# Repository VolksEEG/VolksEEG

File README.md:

# VolksEEG: Acheiving the Promise of Open Source Medical Devices

In a nutshell...

* *The VolksEEG project is creating an open-source
electroencephalogram (EEG) machine, fully-functional for clinical or research use.*

* *The final device will obtain clearance by the USA FDA, and CE marking
(the equivalent of FDA clearance in the EU).*

* *Currently, no other
open-source electronic medical device (that we know of) has full regulatory clearance*

* *All hardware and software designs will be freely available ([free as in speech and as in beer](https://www.howtogeek.com/howto/31717/what-do-the-phrases-free-speech-vs.-free-beer-really-mean)).*

VolksEEG will be the first in a line of open-source medical
devices that will enable a quantum leap in device safety, cost reduction, and innovation.

To sign up for updates about the project, head to [volkseeg.org](https://volkseeg.org).

Here is a video showing the real-time display of 32 waveform channels, from a UI proof-of-concept application:

<https://user-images.githubusercontent.com/58418/132131736-32bca075-f591-47dc-b3fa-c07dddc95de6.mp4>

(The final device will display EEG channels rather than sine waves, of course.)

## Qs & As

You might have a few questions; we have answers, click on the links below to read the:

* [Why are open-source medical devices a good
idea?](#why-are-open-source-medical-devices-a-good-idea)

* [Medical devices? Do you actually know what you're doing?](#do-you-actually-know-what-you-are-doing)

* [Why an EEG machine?](#why-start-with-an-eeg-machine)

* [What needs to be done?](#what-needs-to-be-done)

* [How can I help?](#how-can-i-help)

* [Project planning](#Project-planning)

* [Wait... don't medical devices need to have full requirements and specifications before starting any development?](#where-are-the-detailed-requirements-and-specs)

---

## Why are open-source medical devices a good idea?

Open-source medical devices will provide increased safety, increased
innovation, and reduced device costs.

### Increased Safety

Like all devices, medical devices have become much more complex over
time. *Unlike* all devices, medical devices are often safety- or
life-critical.

As complexity increases, it becomes ever easier to overlook
small design flaws during development, often leading to recalls
later – each year, hundreds of thousands of devices are subject to Class
I recalls, the FDA’s most serious class of recall, reserved for issues
that could cause serious injury or death.

Design flaws are detected by *design reviews*. A core challenge of medical
device safety is ensuring the adequacy of design reviews – both in the
person-hours spent, and the expertise of the reviewers. While design
reviews of proprietary medical devices typically involve only a handful
of reviewers, open-source devices can leverage the eyeballs of myriad
reviewers with a wide variety of expertise; as stated in *The Cathedral
and the Bazaar,* "given enough eyeballs, all bugs are shallow".

### Increased Innovation

Innovation in medical devices is painstakingly slow – compared to
devices from decades ago, most of today’s devices may have more
convenience features, but by-and-large their core functionality is the
same as it was decades ago.

There are several structural issues that impede device innovation. One
of these is the barrier between device companies and
clinicians/researchers. By building proprietary systems using a
conventional profit-only model, manufacturers make it difficult or
impossible for researchers to try new techniques and technologies that
could lead to breakthroughs.

Open-source designs will accelerate innovative research in hospitals and
universities. Investigators will be able to access data from devices,
and even make changes to devices to test new concepts. (To ensure
safety, the FDA and all hospitals have strict rules around how altered
devices can be used.)

In fact... VolksEEG will contain essentially the same circuitry as will be
used in our clinical EEG, and will directly fill a currently-unmet need for research into making anesthesia safer.

### Reduced Device Costs

Medical devices are expensive. There are various reasons for this – some
of these contribute to better patient care, but many don’t. A simple
illustration of this can be seen in the title of a recent journal
article *Prices for Cardiac Implant Devices May Be Up To Six Times
Higher In The US Than In Some European Countries*\[1\]. Frankly, if
device companies couldn’t *profitably* sell devices for one-sixth the
cost… *they wouldn’t*.

Open-source designs will democratize medical devices, resulting in
substantially lower prices. While relatively few companies have the
ability to *design* devices which meet regulatory standards, many more can
manufacture them. A verified design can be adopted by multiple vendors
who otherwise would not be able to develop devices, and competition
reduces pricing. Open-source designs will also enable poorer countries
and NGOs to manufacture their own devices, cutting out costs added by
middle-men.

---

## Do You Actually Know What You Are Doing?

The founding members of VolksEEG are:

* [Bryan Glezerson](https://www.linkedin.com/in/bryan-glezerson-ba71221a9/), a neurosurgical anesthesiologist (Bryan add stuff here).

* [Alan Cohen](https://www.linkedin.com/in/meddev/), an engineer with decades of experience in medical device development (including obtaining FDA clearance and CE marking). Alan is also the author of the book [ProtoType to Product: A Practical Guide for Getting to Market](https://smile.amazon.com/Prototype-Product-Practical-Getting-Market/dp/144936229X/ref=cm_cr_arp_d_product_top?ie=UTF8).

VolksEEG development will result in a safe design which
conforms to US and EU regulations – no different than any other
commercial medical device. Project participants will gain some knowledge
and experience in the medical device design/development processes.

---

## Why start with an EEG machine?

There are two major reasons for an EEG machine being our first product:

### Immediate Need

(Bryan writes this)

## Low-hanging fruit

An EEG machine is relatively simple compared to many other medical
devices, making it a good candidate for a first effort in open-source
devices:

1. Chips are available, e.g. the ADS1299 that we’re using, which are
    purpose-built for EEG use; they are essentially EEGs-on-a-chip that
    greatly reduce the effort needed to develop a full device. These
    components are at the heart of many proprietary EEGs.

2. EEG machines are a lower safety risk than other sophisticated
    medical devices, such as vital signs monitors and infusion pumps. A
    fundamental principal of medical device development is that effort
    should be based on risk. At the start of a project, potential risks
    are identified then addressed in development. Fewer potential risks
    translates into less effort to assure safety.

---

## What needs to be done?

VolksEEG development will have several phases. The first will result in
a “protoduction”\[2\] device to be used for EEG research. The second
will result in a reference design for a full, FDA-clearable device.

A basic block diagram of the prototype system architecture is below:

Other relevant information for nerds ☺️:

* MCU is a nrf52840. Firmware is currently written in Arduino, but
we’ve not yet decided what it will ultimately be. C? C++? Arduino?
Mbed? Also we might want to add an RTOS. Or we might not.

* The MCU and electronics support Bluetooth and NFC – we’re not particularly planning to use these initially, but we like the idea of being able to enable it later by flashing a firmware update.
* The SD card will contain EEG waveforms as standard \*.edf files.For test puposes these files can be read over USB and will appear to the PC application as "real" EEG waveforms.
* The PC software is being developed in C\#, a language that makes good tradeoffs between performance and software reliability.

---

## How can I help?

Development of this prototype breaks down into the following major
tasks:

* Electronics: this is currently staffed
* Firmware: we can use some help
* Software: Several proof-of-concept applications have been written to demonstrate concepts such as reading the serial port at
sufficiently-high speeds, writing 32 real-time waveforms to the
screen in C\#/Windows, and so forth. The next step is to build
the Windows-based spplication software using best practices,
and we would definitely appreciate some help with this.

* Cybersecurity. We could use expertise/help, mainly on the embedded side of things.
* Mechanical: designing and fabricating enclosures. This will be
fairly low effort to start, probably 3D printed. Later we'll likely
use injection molding.
* Regulatory: we have this reasonably under control, but welcome experienced help.
* Quality: this activity will ramp up over time, and we can use some help in writing documentation.

On the software, writing code work we can use a hand in:

* Working with doctors and technicians to understand and document workflow so our software can work the way our customers want.

* UI/UxD design.

Some non-engineering help we could use:

* Web site development
* Social media
* Fundraising
* Business development
* Legal
* Business issues
* IP issues

<!-- end list -->

---

## Where are the detailed requirements and specs?

The short story is that our initial effort will be a highly-functional prototype, not a medical device.

When a medical device is cleared by the FDA, it's required that there be
detailed requirements and specifications, and that development and testing
has proceeded deliberately to meet those requirements and specifications.

Medical device development uses relatively-heavyweight development processes
(i.e., there's a good bit of documentation, traceability matrices, etc) that
the FDA generally refers to as design controls. If development only proceeds
after writing and reviewing formal requirements/architecture/specs etc., we run
the risk of finding technical surprises that will cause us to back up and update
those requirements/architecture/specs that we worked so hard on. So, to avoid
wasted effort in creating requirements/architecture/specs that might get changed
later, it often makes sense to start by building a fairly-functional prototype
without using full medical-grade design controls, then once that's working to
circle back and redo the process using design controls. This usually ends up
reusing the designs produced during the prototype build, but now we document
and otherwise control them properly.

---

## Endnotes

1. Wenzl, Martin, and Elias Mossialos. “Prices For Cardiac Implant
   Devices May Be Up To Six Times Higher In The US Than In Some
   European Countries.” *Health Affairs*, vol. 37, no. 10, Oct. 2018,
   pp. 1570–77, doi:10.1377/hlthaff.2017.1367.

2. *Protoduction* refers to a device that is somewhere between
    prototype and production devices: far enough along that it can be
    used for its intended use, but not a fully-developed commercial
    product. Production quantities are typically low, in the ones or
    tens.

## For more information on VolksEEG (beyond this readme)

* Further technical details may be found on [our wiki](https://github.com/VolksEEG/VolksEEG/wiki).

* The start of a detailed project overview may be found [here](https://1drv.ms/w/s!AvEzNsBMxiAcpMBu5GTByJBZlJbeDA?e=k30pK4).

* Our repositories may be found on Github [here](https://github.com/VolksEEG/).

* The Firmware repository may be found [here](https://github.com/VolksEEG/eeg-device-firmware).

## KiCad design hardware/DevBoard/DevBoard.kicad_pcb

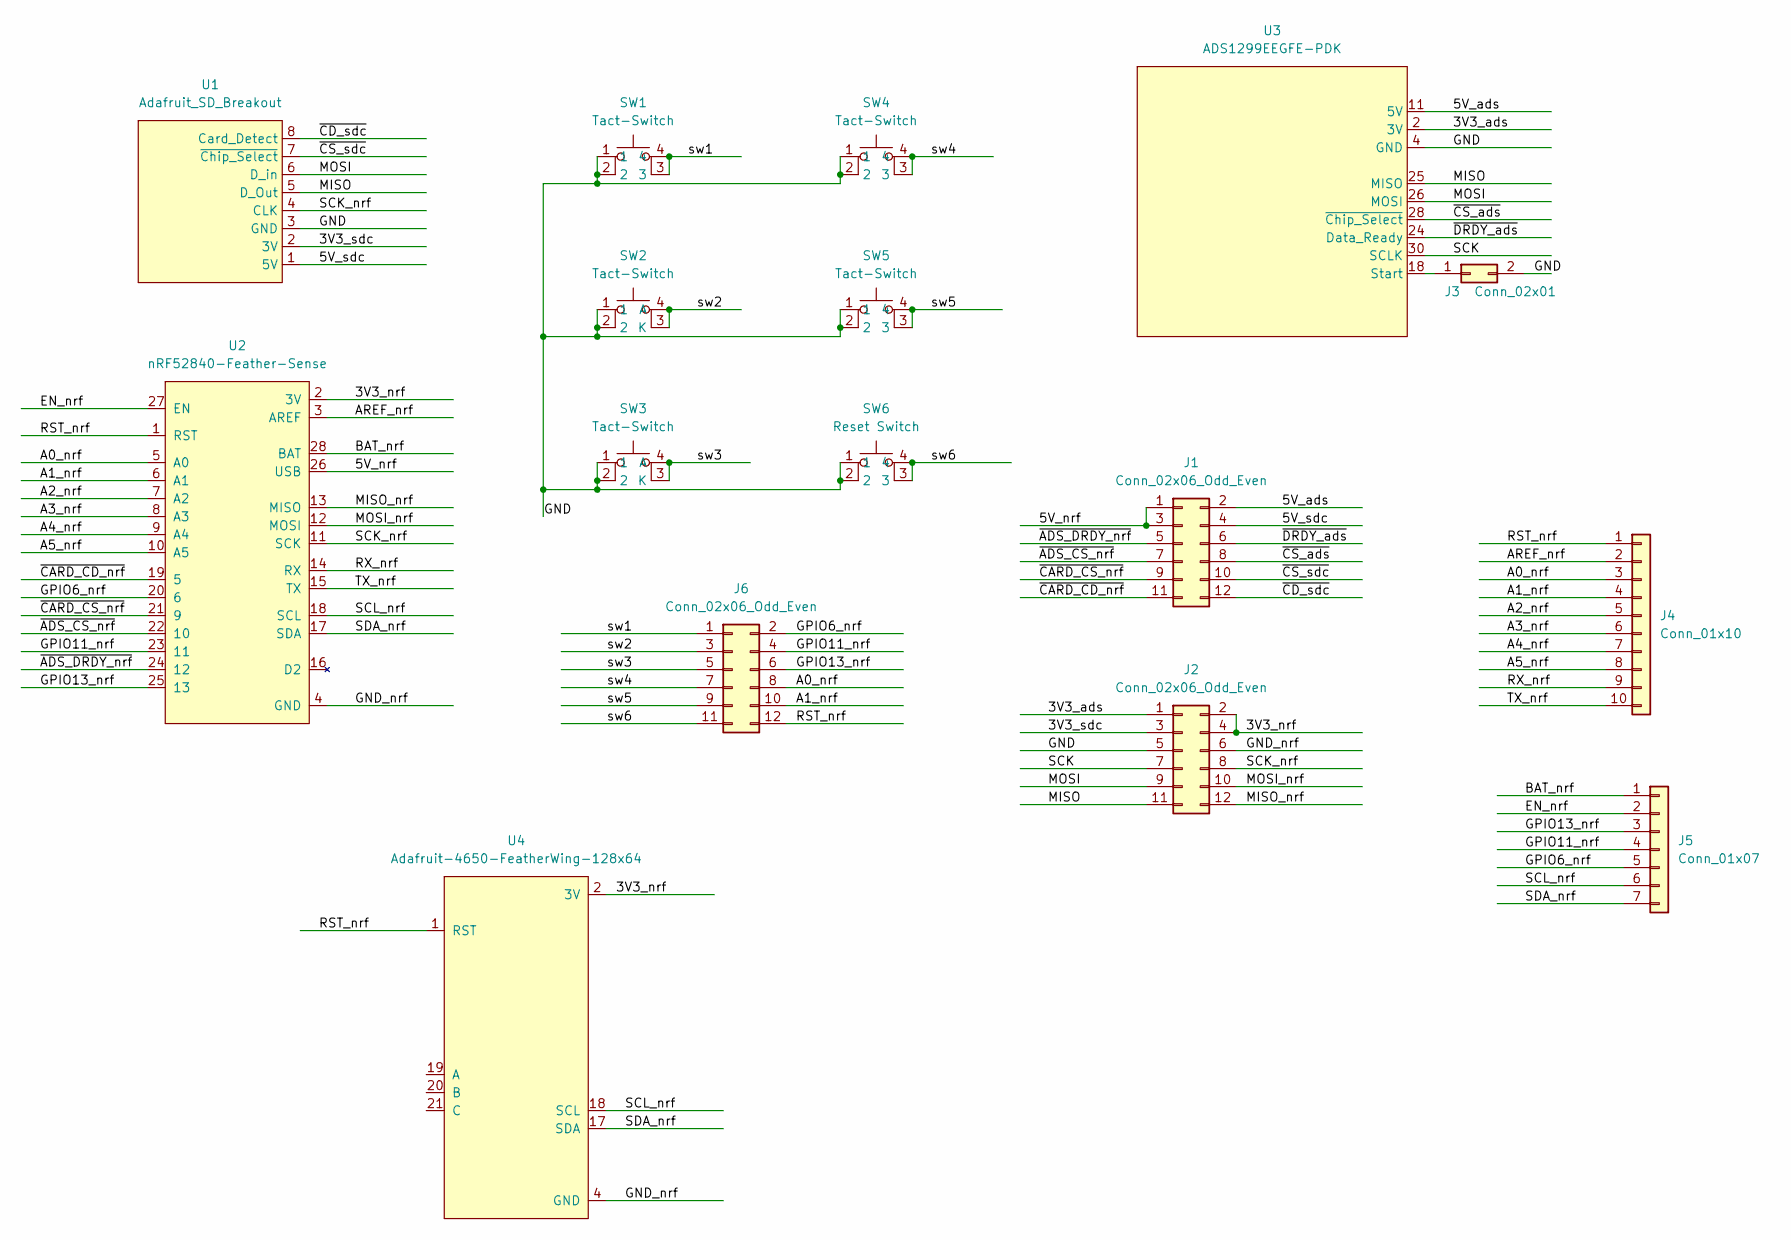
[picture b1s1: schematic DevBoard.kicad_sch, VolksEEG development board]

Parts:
J1, J2: Conn_02x06_Odd_Even; PinHeader_2x06_P2.54mm_Vertical
J3: Conn_02x01; PinHeader_1x02_P2.54mm_Vertical
J4: Conn_01x10; PinHeader_1x10_P2.54mm_Vertical
J5: Conn_01x07; PinHeader_1x07_P2.54mm_Vertical
J6: Conn_02x06_Odd_Even; 6-Jumper Header
SW1, SW2, SW3, SW4, SW5: Tact-Switch; Sparkfun Tactile Switch
SW6: Reset Switch; Sparkfun Tactile Switch
U1: Adafruit_SD_Breakout; Part Number 254
U2: nRF52840-Feather-Sense; nRF52840_Feather_Sense
U3: ADS1299EEGFE-PDK
U4: Adafruit-4650-FeatherWing-128x64; nRF52840_Feather_Sense

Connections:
/3V3_ads: J2.1, U3.2 (3V)
/3V3_nrf: J2.2, J2.4, U2.2 (3V), U4.2 (3V)
/3V3_sdc: J2.3, U1.2 (3V)
/5V_ads: J1.2, U3.11 (5V)
/5V_nrf: J1.1, J1.3, U2.26 (USB)
/5V_sdc: J1.4, U1.1 (5V)
/A0_nrf: J4.3, J6.8, U2.5 (A0)
/A1_nrf: J4.4, J6.10, U2.6 (A1)
/A2_nrf: J4.5, U2.7 (A2)
/A3_nrf: J4.6, U2.8 (A3)
/A4_nrf: J4.7, U2.9 (A4)
/A5_nrf: J4.8, U2.10 (A5)
/AREF_nrf: J4.2, U2.3 (AREF)
/BAT_nrf: J5.1, U2.28 (BAT)
/EN_nrf: J5.2, U2.27 (EN)
/GND: J2.5, J3.2, SW1.1, SW1.2, SW2.1, SW2.2, SW3.1, SW3.2, SW4.1, SW4.2, SW5.1, SW5.2, SW6.1, SW6.2, U1.3 (GND), U3.4 (GND)
/GND_nrf: J2.6, U2.4 (GND), U4.4 (GND)
/GPIO6_nrf: J5.5, J6.2, U2.20 (6)
/GPIO11_nrf: J5.4, J6.4, U2.23 (11)
/GPIO13_nrf: J5.3, J6.6, U2.25 (13)
/MISO: J2.11, U1.5 (D_Out), U3.25 (MISO)
/MISO_nrf: J2.12, U2.13 (MISO)
/MOSI: J2.9, U1.6 (D_in), U3.26 (MOSI)
/MOSI_nrf: J2.10, U2.12 (MOSI)
/RST_nrf: J4.1, J6.12, U2.1 (RST), U4.1 (RST)
/RX_nrf: J4.9, U2.14 (RX)
/SCK: J2.7, U3.30 (SCLK)
/SCK_nrf: J2.8, U1.4 (CLK), U2.11 (SCK)
/SCL_nrf: J5.6, U2.18 (SCL), U4.18 (SCL)
/SDA_nrf: J5.7, U2.17 (SDA), U4.17 (SDA)
/TX_nrf: J4.10, U2.15 (TX)
/sw1: J6.1, SW1.3, SW1.4
/sw2: J6.3, SW2.3 (K), SW2.4 (A)
/sw3: J6.5, SW3.3 (K), SW3.4 (A)
/sw4: J6.7, SW4.3, SW4.4
/sw5: J6.9, SW5.3, SW5.4
/sw6: J6.11, SW6.3, SW6.4
/~ADS_CS_nrf: J1.7, U2.22 (10)
/~ADS_DRDY_nrf: J1.5, U2.24 (12)
/~CARD_CD_nrf: J1.11, U2.19 (5)
/~CARD_CS_nrf: J1.9, U2.21 (9)
/~CD_sdc: J1.12, U1.8 (Card_Detect)
/~CS_ads: J1.8, U3.28 (~Chip_Select)
/~CS_sdc: J1.10, U1.7 (~Chip_Select)
/~DRDY_ads: J1.6, U3.24 (Data_Ready)
unnamed: J3.1, U3.18 (Start)

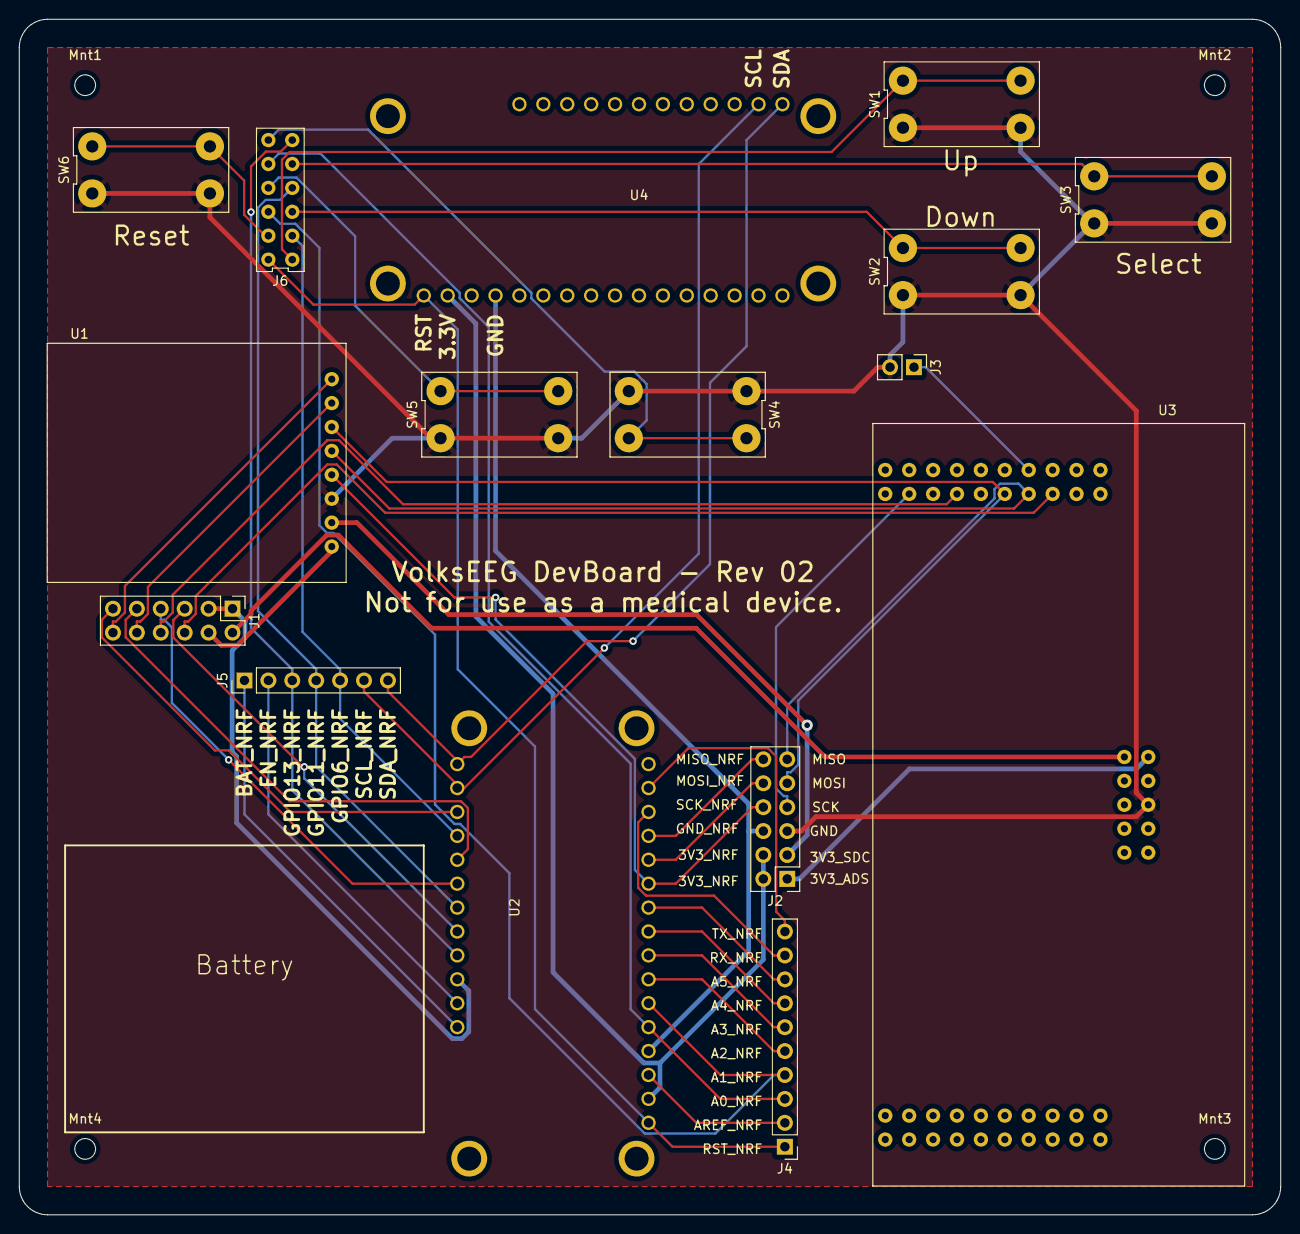
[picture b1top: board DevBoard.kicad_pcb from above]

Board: 2 copper layers, 134.0 x 127.0 mm, 20 parts (0 on the bottom side), 46 nets.

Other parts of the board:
Mnt1, Mnt2, Mnt3, Mnt4: MountingHole_2.2mm_M2

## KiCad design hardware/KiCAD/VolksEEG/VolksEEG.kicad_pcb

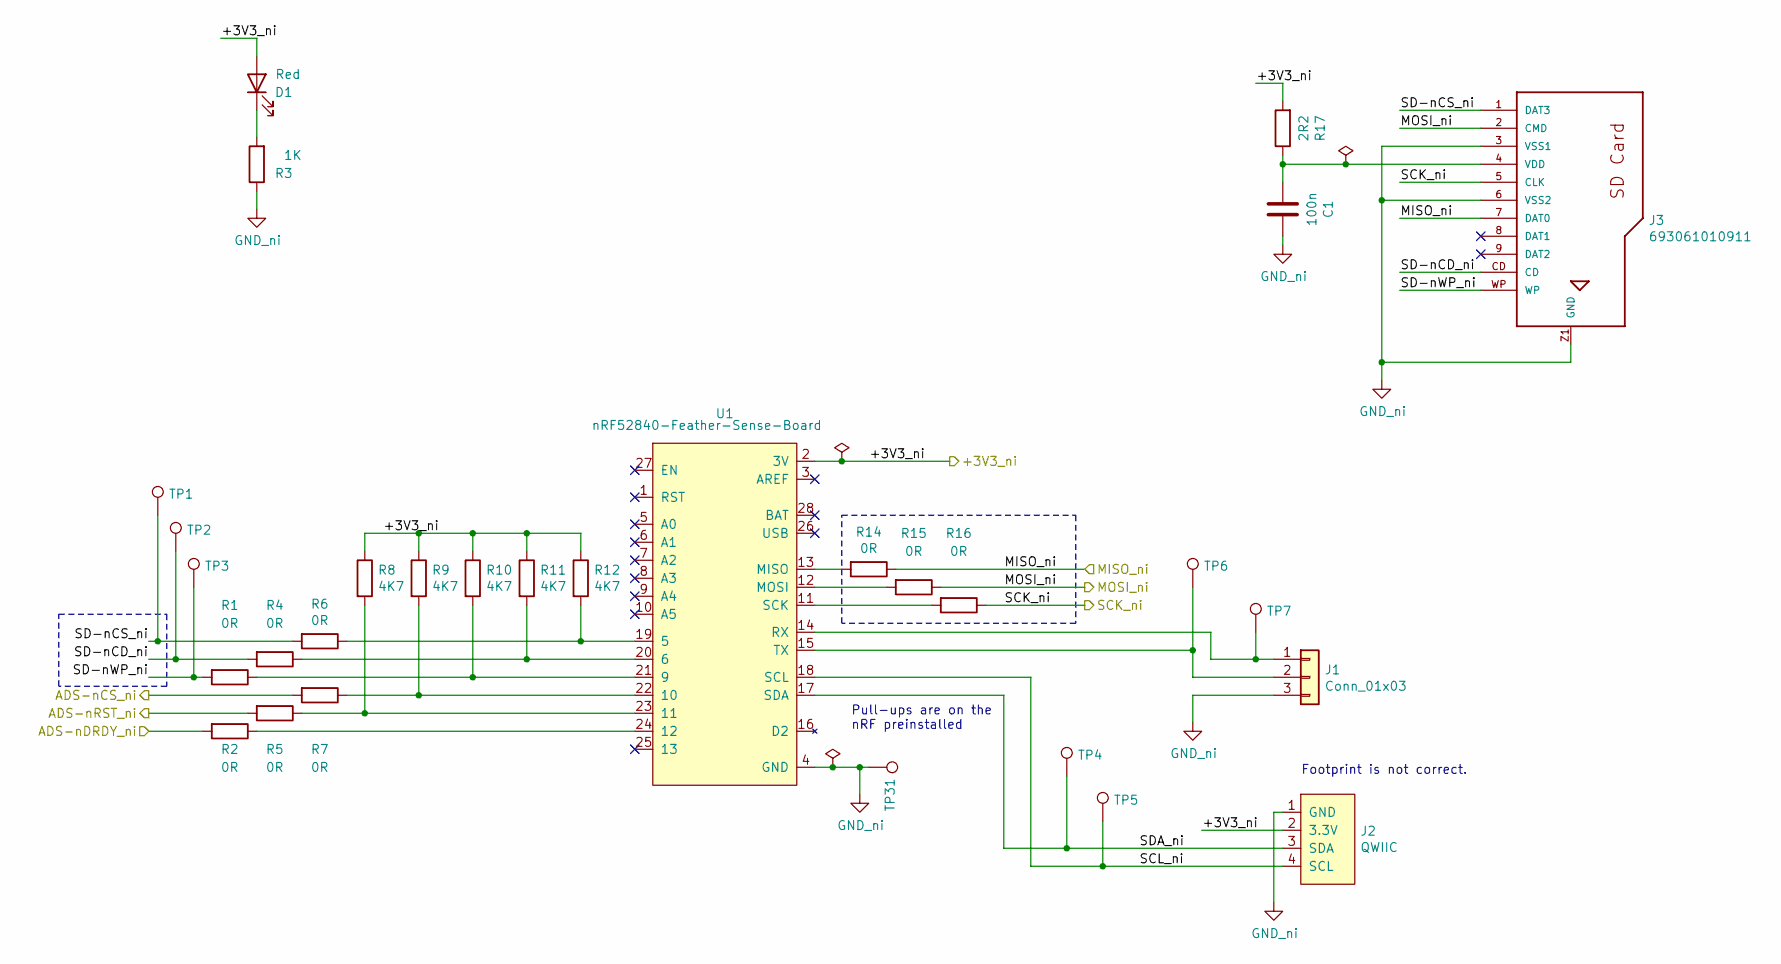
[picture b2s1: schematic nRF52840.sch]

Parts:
C1: 100n; C_0603_1608Metric_Pad1.08x0.95mm_HandSolder; Part Number CL21B104KACNNNC
D1: Red; LED_0603_1608Metric_Pad1.05x0.95mm_HandSolder; Part Number VFHR1111C-3BY2A-TR
J1: Conn_01x03; PinHeader_1x03_P2.54mm_Vertical; Part Number 640456-3
J2: QWIIC; PinHeader_1x04_P2.54mm_Vertical; Part Number 640456-4
J3: 693061010911; Part Number 693061010911
R1, R2, R4, R5, R6, R7, R14, R15, R16: 0R; R_0603_1608Metric_Pad0.98x0.95mm_HandSolder; Part Number TRR03EZPJ000
R3: 1K; R_0603_1608Metric_Pad0.98x0.95mm_HandSolder; Part Number RMCF0603FG1K00
R8, R9, R10, R11, R12: 4K7; R_0603_1608Metric_Pad0.98x0.95mm_HandSolder; Part Number RMCF0603FT4K70
R17: 2R2; high_power_chip_resistor; Part Number 35502R2JT
TP1, TP2, TP3, TP4, TP5, TP6, TP7: TestPoint; TestPoint_Keystone_5010-5014_Multipurpose; Part Number N/A
TP31: TestPoint; TestPoint_Bridge_Pitch7.62mm_Drill1.3mm; Part Number N/A
U1: nRF52840-Feather-Sense-Board; nRF52840_Feather_Sense; Part Number 4516

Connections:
/Isolation/+3V3_ni: D1.2 (A), J2.2 (3.3V), R8.1, R9.1, R10.1, R11.1, R12.1, R17.2, U1.2 (3V); also elsewhere on the board
/Isolation/MISO_ni: J3.7 (DAT0), R14.1; also elsewhere on the board
/Isolation/MOSI_ni: J3.2 (CMD), R15.1; also elsewhere on the board
/Isolation/SCK_ni: J3.5 (CLK), R16.1; also elsewhere on the board
/nRF52840 Feather Sense Express Board/ADS-nCS_ni: R7.2; also elsewhere on the board
/nRF52840 Feather Sense Express Board/ADS-nDRDY_ni: R2.2; also elsewhere on the board
/nRF52840 Feather Sense Express Board/ADS-nRST_ni: R5.2; also elsewhere on the board
/nRF52840 Feather Sense Express Board/SCL_ni: J2.4 (SCL), TP5.1, U1.18 (SCL)
/nRF52840 Feather Sense Express Board/SD-nCD_ni: J3.CD, R4.2, TP2.1
/nRF52840 Feather Sense Express Board/SD-nCS_ni: J3.1 (DAT3), R6.2, TP1.1
/nRF52840 Feather Sense Express Board/SD-nWP_ni: J3.WP, R1.2, TP3.1
/nRF52840 Feather Sense Express Board/SDA_ni: J2.3 (SDA), TP4.1, U1.17 (SDA)
GND: C1.1, J1.3, J2.1 (GND), J3.3 (VSS1), J3.6 (VSS2), J3.Z1 (GND), J3.Z2 (GND), R3.1, TP31.1, U1.4 (GND); also elsewhere on the board
unnamed: C1.2, J3.4 (VDD), R17.1
unnamed: D1.1 (K), R3.2
unnamed: J1.1, TP7.1, U1.14 (RX)
unnamed: J1.2, TP6.1, U1.15 (TX)
unnamed: R1.1, R10.2, U1.21 (9)
unnamed: R2.1, U1.24 (12)
unnamed: R5.1, R8.2, U1.23 (11)
unnamed: R7.1, R9.2, U1.22 (10)
unnamed: R4.1, R11.2, U1.20 (6)
unnamed: R6.1, R12.2, U1.19 (5)
unnamed: R14.2, U1.13 (MISO)
unnamed: R15.2, U1.12 (MOSI)
unnamed: R16.2, U1.11 (SCK)

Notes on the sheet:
Pull-ups are on the nRF preinstalled
Footprint is not correct.

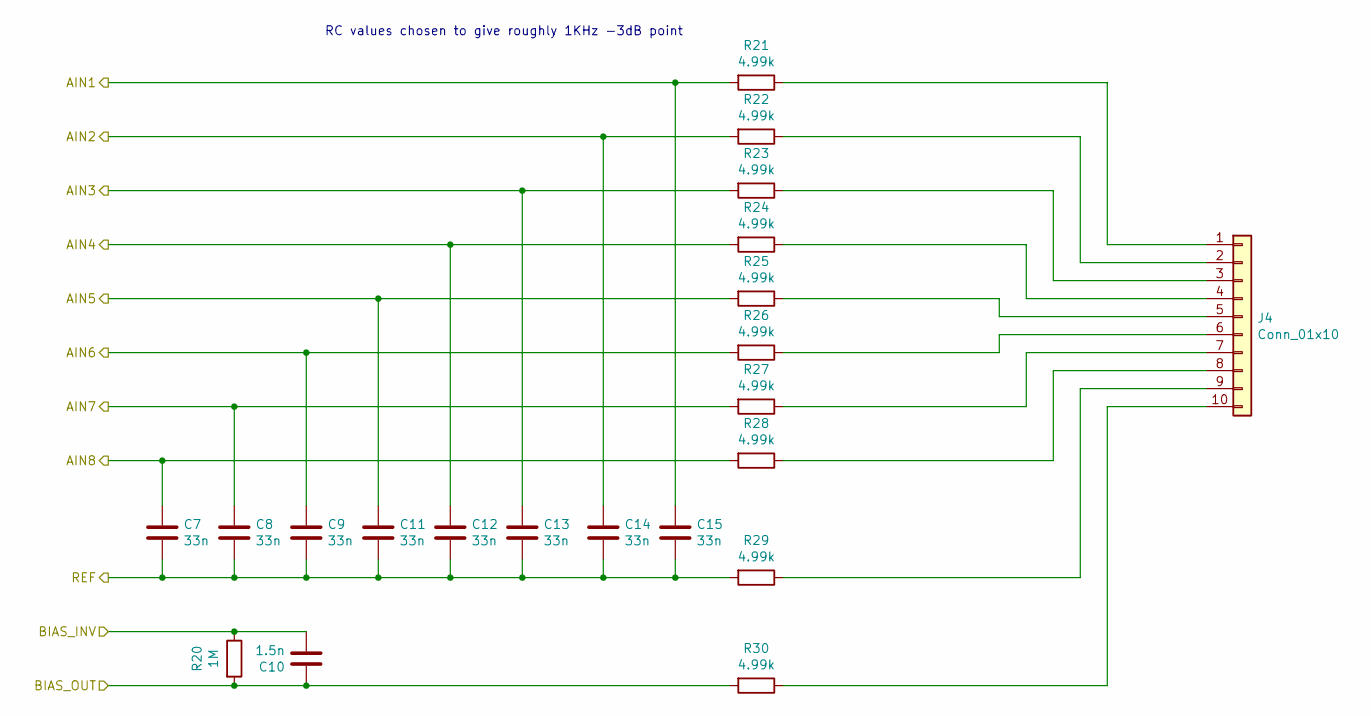
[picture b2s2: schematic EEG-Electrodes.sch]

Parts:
C7, C8, C9, C11, C12, C13, C14, C15: 33n; C_0805_2012Metric_Pad1.18x1.45mm_HandSolder; Part Number C0805C333F3GEC7210
C10: 1.5n; C_0603_1608Metric_Pad1.08x0.95mm_HandSolder; Part Number 08055A152FAT2A
J4: Conn_01x10; PinHeader_1x10_P2.54mm_Vertical; Part Number 1-640456-0
R20: 1M; R_0603_1608Metric_Pad0.98x0.95mm_HandSolder
R21, R22, R23, R24, R25, R26, R27, R28, R29, R30: 4.99k; R_0603_1608Metric_Pad0.98x0.95mm_HandSolder

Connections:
/ADS1299/AIN1: C15.1, R21.2; also elsewhere on the board
/ADS1299/AIN2: C14.1, R22.2; also elsewhere on the board
/ADS1299/AIN3: C13.1, R23.2; also elsewhere on the board
/ADS1299/AIN4: C12.1, R24.2; also elsewhere on the board
/ADS1299/AIN5: C11.1, R25.2; also elsewhere on the board
/ADS1299/AIN6: C9.1, R26.2; also elsewhere on the board
/ADS1299/AIN7: C8.1, R27.2; also elsewhere on the board
/ADS1299/AIN8: C7.1, R28.2; also elsewhere on the board
/ADS1299/BIAS_INV: C10.2, R20.1; also elsewhere on the board
/ADS1299/BIAS_OUT: C10.1, R20.2, R30.2; also elsewhere on the board
/ADS1299/REF: C7.2, C8.2, C9.2, C11.2, C12.2, C13.2, C14.2, C15.2, R29.2; also elsewhere on the board
unnamed: J4.1, R21.1
unnamed: J4.2, R22.1
unnamed: J4.3, R23.1
unnamed: J4.4, R24.1
unnamed: J4.5, R25.1
unnamed: J4.6, R26.1
unnamed: J4.7, R27.1
unnamed: J4.8, R28.1
unnamed: J4.9, R29.1
unnamed: J4.10, R30.1

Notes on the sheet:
RC values chosen to give roughly 1KHz -3dB point

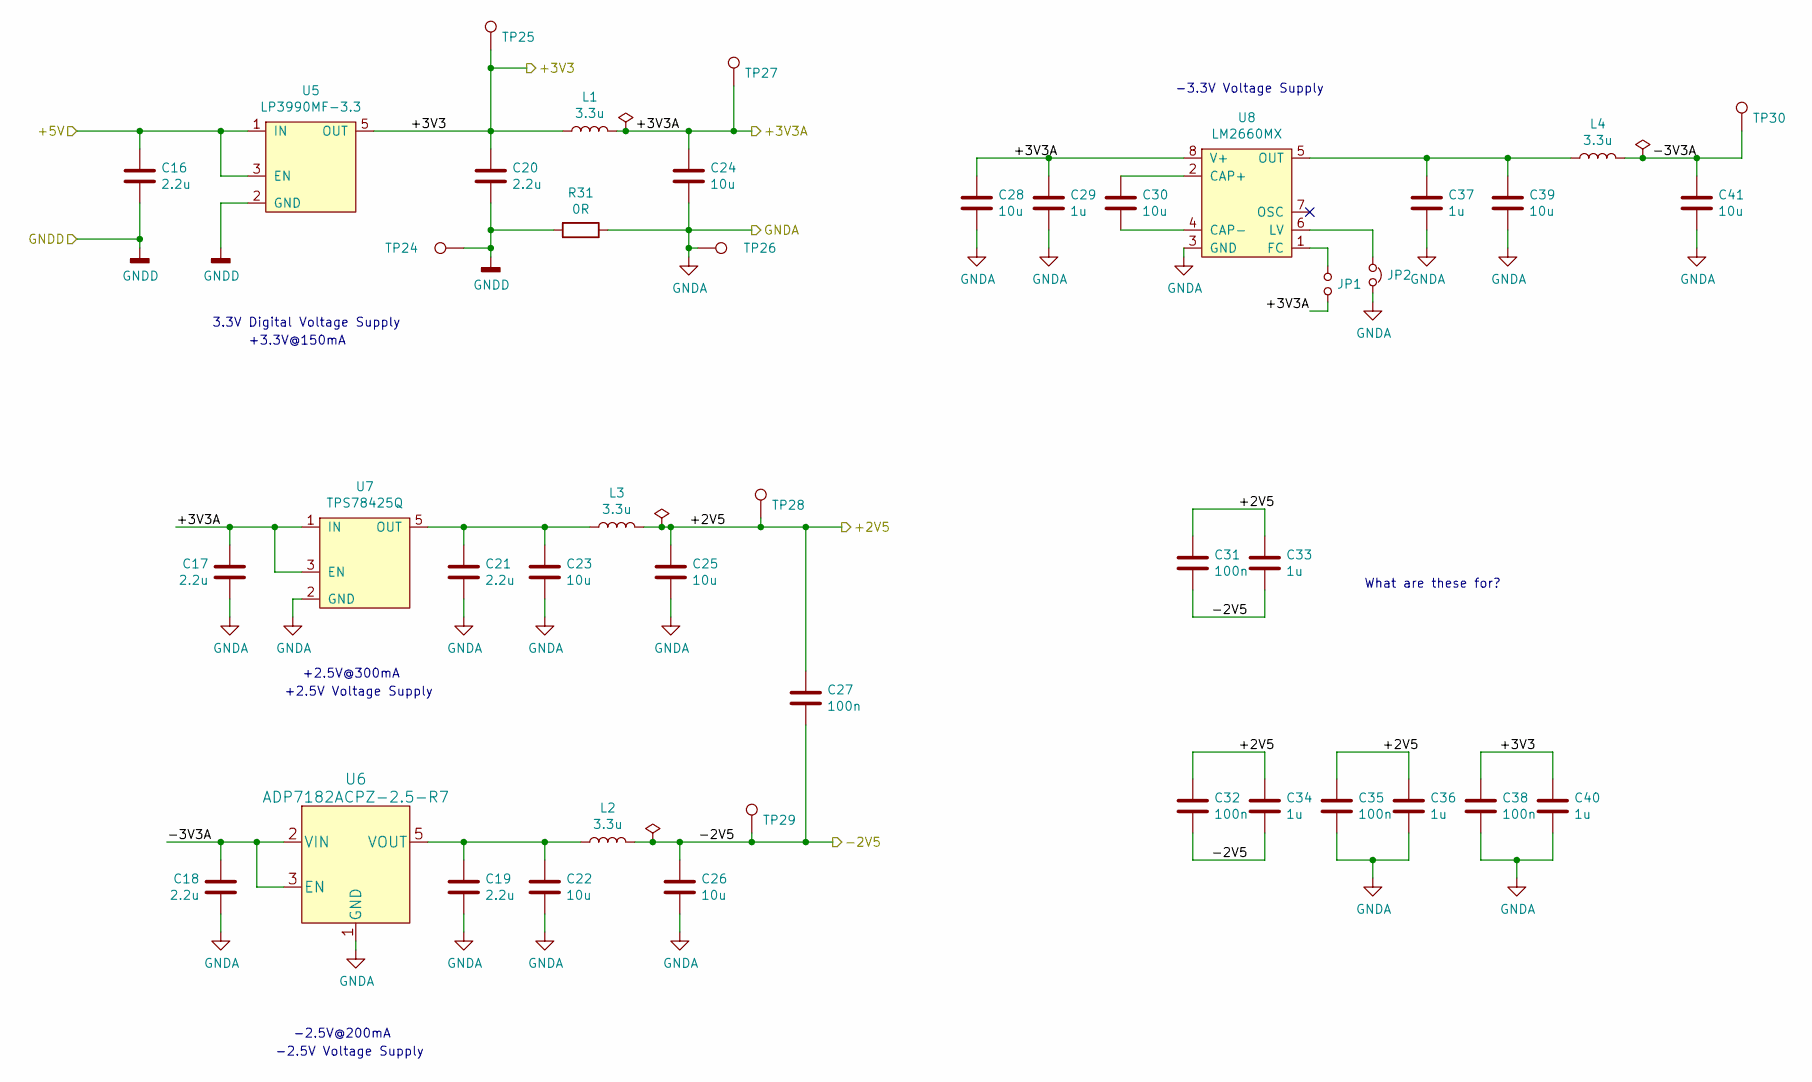
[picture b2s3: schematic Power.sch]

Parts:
C16, C17, C18, C19, C20, C21: 2.2u; C_0603_1608Metric_Pad1.08x0.95mm_HandSolder; Part Number CL21B225KAFNFNE
C22, C23, C24, C25, C26, C28, C30, C39, C41: 10u; C_0603_1608Metric_Pad1.08x0.95mm_HandSolder; Part Number CL21B106KPQNNNE
C27, C31, C32, C35, C38: 100n; C_0603_1608Metric_Pad1.08x0.95mm_HandSolder; Part Number CL21B104KACNNNC
C29, C33, C34, C36, C37, C40: 1u; C_0603_1608Metric_Pad1.08x0.95mm_HandSolder; Part Number CL21B105KAFNNNE
JP1: Jumper_NO_Small; SolderJumper-2_P1.3mm_Open_Pad1.0x1.5mm; Part Number N/A
JP2: Jumper_NC_Small; SolderJumper-2_P1.3mm_Bridged_Pad1.0x1.5mm; Part Number N/A
L1, L2, L3, L4: 3.3u; L_0805_2012Metric_Pad1.15x1.40mm_HandSolder; Part Number MLZ2012A3R3WTD25
R31: 0R; R_0603_1608Metric_Pad0.98x0.95mm_HandSolder; Part Number TRR03EZPJ000
TP24, TP26: TestPoint; TestPoint_Bridge_Pitch7.62mm_Drill1.3mm; Part Number N/A
TP25, TP27, TP28, TP29, TP30: TestPoint; TestPoint_Keystone_5010-5014_Multipurpose; Part Number N/A
U5: LP3990MF-3.3; SOT-23-5_HandSoldering; Part Number LP3990MF-3.3
U6: ADP7182ACPZ-2.5-R7; TSOT-23-5; Part Number ADP7182ACPZN-2.5R7
U7: TPS78425Q; SOT-23-5_HandSoldering; Part Number TPS78425QDBVRQ1
U8: LM2660MX; SOIC127P599X175-8N; Part Number LM2660MX

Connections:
/ADS1299 Power/+2V5: C25.1, C27.1, C31.1, C32.1, C33.1, C34.1, C35.1, C36.1, L3.2, TP28.1; also elsewhere on the board
/ADS1299 Power/+3V3: C20.1, C38.1, C40.1, L1.1, TP25.1, U5.5 (OUT); also elsewhere on the board
/ADS1299 Power/+3V3A: C17.1, C24.1, C28.1, C29.1, JP1.2, L1.2, TP27.1, U7.1 (IN), U7.3 (EN), U8.8 (V+); also elsewhere on the board
/ADS1299 Power/+5V: C16.1, U5.1 (IN), U5.3 (EN); also elsewhere on the board
/ADS1299 Power/-2V5: C26.1, C27.2, C31.2, C32.2, C33.2, C34.2, L2.2, TP29.1; also elsewhere on the board
/ADS1299 Power/-3V3A: C18.1, C41.1, L4.2, TP30.1, U6.2 (VIN), U6.3 (EN)
GNDA: C17.2, C18.2, C19.2, C21.2, C22.2, C23.2, C24.2, C25.2, C26.2, C28.2, C29.2, C35.2, C36.2, C37.2, C38.2, C39.2, C40.2, C41.2, JP2.2, R31.1, TP26.1, U6.1 (GND), U7.2 (GND), U8.3 (GND); also elsewhere on the board
GNDD: C16.2, C20.2, R31.2, TP24.1, U5.2 (GND); also elsewhere on the board
unnamed: C19.1, C22.1, L2.1, U6.5 (VOUT)
unnamed: C21.1, C23.1, L3.1, U7.5 (OUT)
unnamed: C30.1, U8.2 (CAP+)
unnamed: C30.2, U8.4 (CAP-)
unnamed: C37.1, C39.1, L4.1, U8.5 (OUT)
unnamed: JP1.1, U8.1 (FC)
unnamed: JP2.1, U8.6 (LV)

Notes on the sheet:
+2.5V Voltage Supply
+2.5V@300mA
-2.5V@200mA
-3.3V Voltage Supply
3.3V Digital Voltage Supply
-2.5V Voltage Supply
+3.3V@150mA
What are these for?

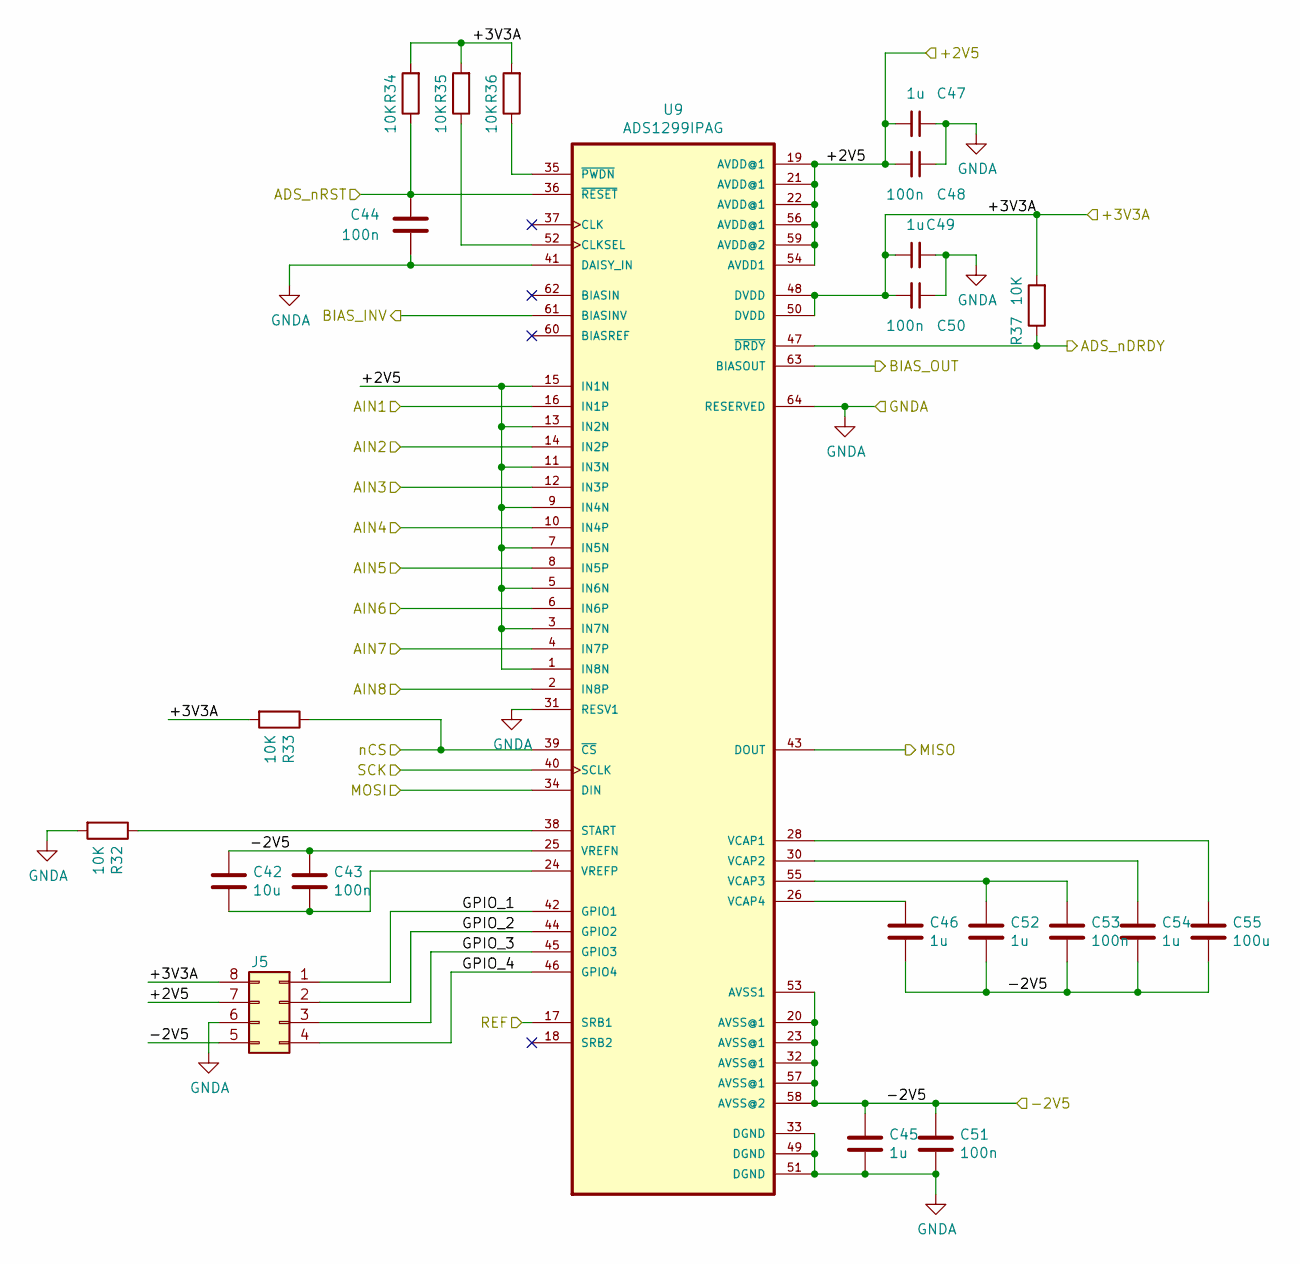
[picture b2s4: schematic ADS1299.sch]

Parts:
C42: 10u; C_0603_1608Metric_Pad1.08x0.95mm_HandSolder; Part Number CL21B106KPQNNNE
C43, C44, C48, C50, C51, C53: 100n; C_0603_1608Metric_Pad1.08x0.95mm_HandSolder; Part Number CL21B104KACNNNC
C45, C46, C47, C49, C52, C54: 1u; C_0603_1608Metric_Pad1.08x0.95mm_HandSolder; Part Number CL21B105KAFNNNE
C55: 100u; C_1210_3225Metric_Pad1.33x2.70mm_HandSolder; Part Number LMK325ABJ107MMHP
J5: Conn_02x04_Counter_Clockwise; PinHeader_2x04_P2.54mm_Vertical; Part Number 5-146256-4
R32, R33, R34, R35, R36, R37: 10K; R_0603_1608Metric_Pad0.98x0.95mm_HandSolder; Part Number RMCF0603JT10K0
U9: ADS1299IPAG; LQFP-64_10x10mm_P0.5mm; Part Number ADS1299IPAG

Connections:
/ADS1299 Power/+2V5: C47.2, C48.2, J5.7, U9.1 (IN8N), U9.3 (IN7N), U9.5 (IN6N), U9.7 (IN5N), U9.9 (IN4N), U9.11 (IN3N), U9.13 (IN2N), U9.15 (IN1N), U9.19 (AVDD@1), U9.21 (AVDD@1), U9.22 (AVDD@1), U9.54 (AVDD1), U9.56 (AVDD@1), U9.59 (AVDD@2); also elsewhere on the board
/ADS1299 Power/+3V3A: C49.1, C50.2, J5.8, R33.2, R34.2, R35.2, R36.2, R37.2, U9.48 (DVDD), U9.50 (DVDD); also elsewhere on the board
/ADS1299 Power/-2V5: C42.1, C43.1, C45.1, C46.2, C51.1, C52.2, C53.2, C54.2, C55.2, J5.5, U9.20 (AVSS@1), U9.23 (AVSS@1), U9.25 (VREFN), U9.32 (AVSS@1), U9.53 (AVSS1), U9.57 (AVSS@1), U9.58 (AVSS@2); also elsewhere on the board
/ADS1299/ADS_nDRDY: R37.1, U9.47 (~DRDY); also elsewhere on the board
/ADS1299/ADS_nRST: C44.2, R34.1, U9.36 (~RESET); also elsewhere on the board
/ADS1299/AIN1: U9.16 (IN1P); also elsewhere on the board
/ADS1299/AIN2: U9.14 (IN2P); also elsewhere on the board
/ADS1299/AIN3: U9.12 (IN3P); also elsewhere on the board
/ADS1299/AIN4: U9.10 (IN4P); also elsewhere on the board
/ADS1299/AIN5: U9.8 (IN5P); also elsewhere on the board
/ADS1299/AIN6: U9.6 (IN6P); also elsewhere on the board
/ADS1299/AIN7: U9.4 (IN7P); also elsewhere on the board
/ADS1299/AIN8: U9.2 (IN8P); also elsewhere on the board
/ADS1299/BIAS_INV: U9.61 (BIASINV); also elsewhere on the board
/ADS1299/BIAS_OUT: U9.63 (BIASOUT); also elsewhere on the board
/ADS1299/GPIO_1: J5.1, U9.42 (GPIO1)
/ADS1299/GPIO_2: J5.2, U9.44 (GPIO2)
/ADS1299/GPIO_3: J5.3, U9.45 (GPIO3)
/ADS1299/GPIO_4: J5.4, U9.46 (GPIO4)
/ADS1299/MISO: U9.43 (DOUT); also elsewhere on the board
/ADS1299/MOSI: U9.34 (DIN); also elsewhere on the board
/ADS1299/REF: U9.17 (SRB1); also elsewhere on the board
/ADS1299/SCK: U9.40 (SCLK); also elsewhere on the board
/ADS1299/nCS: R33.1, U9.39 (~CS); also elsewhere on the board
GNDA: C44.1, C45.2, C47.1, C48.1, C49.2, C50.1, C51.2, J5.6, R32.2, U9.31 (RESV1), U9.33 (DGND), U9.41 (DAISY_IN), U9.49 (DGND), U9.51 (DGND), U9.64 (RESERVED); also elsewhere on the board
unnamed: C42.2, C43.2, U9.24 (VREFP)
unnamed: C46.1, U9.26 (VCAP4)
unnamed: C52.1, C53.1, U9.55 (VCAP3)
unnamed: C54.1, U9.30 (VCAP2)
unnamed: C55.1, U9.28 (VCAP1)
unnamed: R32.1, U9.38 (START)
unnamed: R35.1, U9.52 (CLKSEL)
unnamed: R36.1, U9.35 (~PWDN)
